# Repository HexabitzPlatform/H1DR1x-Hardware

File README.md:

# H1DR1x-Hardware
Hexabitz RS485 Serial Transceiver Module Hardware Design

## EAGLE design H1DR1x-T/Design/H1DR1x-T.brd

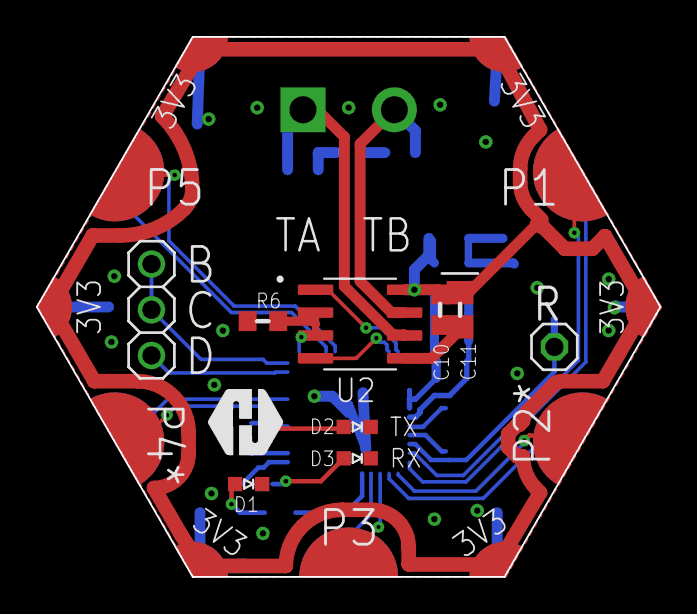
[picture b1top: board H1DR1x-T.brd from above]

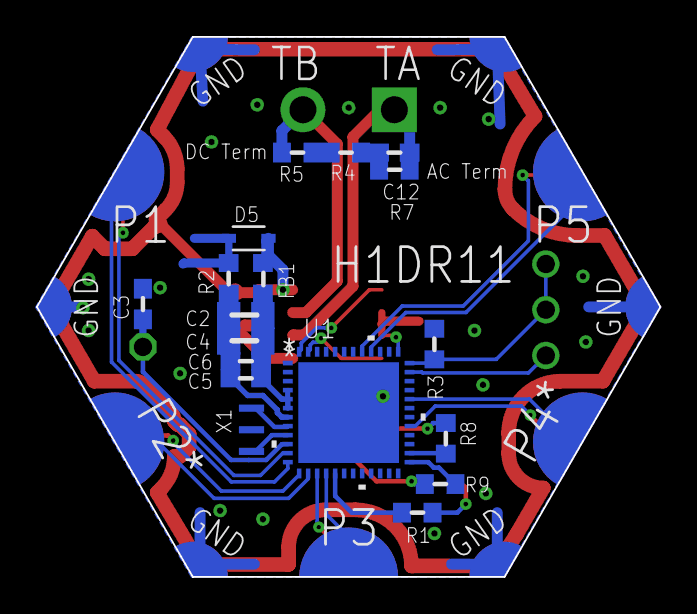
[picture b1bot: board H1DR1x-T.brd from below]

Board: 2 copper layers, 34.6 x 30.0 mm, 30 parts (18 on the bottom side), 32 nets.

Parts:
C2: 1uF; C-0805
C3, C5, C6, C10, C12: 100nF; C-0603
C4: 4.7uF; C-0805
C11: 4.7uF; C-0805-POL
D1: RED; VLMS1300-GS08
D2: YELLOW; VLMS1300-GS08
D3: ORANGE; VLMS1300-GS08
D5: BOURNS_CDSOD323-T03SCBOURNS_CDSOD323-T03SC_0_0; BOURNS_CDSOD323-T03SC_0
FB1: FB-TDK_MMZ1608Y300B; FB-0603
P1: HEXABIT_17.32_NO_P6
P2: RS-485; 1546111-2
R: R; 1X01
R1, R8, R9: 270R; R-0603
R2, R4, R7: 0.0R; R-0603
R3: 10K; R-0603
R5: 120R; R-0603
R6: 10k; R-0603
SWD: 1X03
TRIMBLE-LOGO1: HEXA-LOGO
U1: STM32G0B1CEU6QFN_B1CEU6_STM-L; QFN_B1CEU6_STM-L
U2: MAX14840EASA+T; SOIC127P600X175-8N
X1: XTALL_CSTCE8M00G52

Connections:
CLK: R3.2, SWD.1, SWD.2, U1.36
DATA: SWD.3, U1.35
GND: C3.2, C10.2, C11.2, D1.C, D2.C, D3.C, D5.1, P1.PAD_PD7, P1.PAD_PD8, P1.PAD_PD9, P1.PAD_PD10, P1.PAD_PD11, P1.PAD_PD12, R2.1, R3.1, R6.2, U1.49, U2.5, X1.P$2
unnamed: D1.A, R1.2
unnamed: C12.2, R4.2, R7.1
unnamed: R1.1, U1.17
unnamed: C3.1, R.1, U1.10
unnamed: U1.9, X1.P$1
unnamed: U1.8, X1.P$3
unnamed: R4.1, R5.2
unnamed: D3.A, R9.1
unnamed: D2.A, R8.1
RX_LED: R9.2, U1.25
TA: C12.1, P2.1, R7.2, U2.6
TB: P2.2, R5.1, U2.7
TX_LED: R8.2, U1.26
USART1_RX: P1.PAD_PD4, U1.32
USART1_TX: P1.PAD_PU4, U1.29
USART2_RX: P1.PAD_PD2, U1.14
USART2_TX: P1.PAD_PU2, U1.13
USART3_RTS: R6.1, U1.37, U2.2, U2.3
USART3_RX: U1.48, U2.1
USART3_TX: U1.47, U2.4
USART4_RX: P1.PAD_PD1, U1.12
USART4_TX: P1.PAD_PU1, U1.11
USART5_RX: P1.PAD_PD5, U1.40
USART5_TX: P1.PAD_PU5, U1.41
USART6_RX: P1.PAD_PD3, U1.16
USART6_TX: P1.PAD_PU3, U1.15
VDD: C10.1, C11.1, D5.2, FB1.2, P1.PAD_PU7, P1.PAD_PU8, P1.PAD_PU9, P1.PAD_PU10, P1.PAD_PU11, P1.PAD_PU12, U2.8
VDDA: C2.1, C4.1, C5.1, C6.1, FB1.1, U1.4, U1.5, U1.6
VSSA: C2.2, C4.2, C5.2, C6.2, R2.2, U1.7

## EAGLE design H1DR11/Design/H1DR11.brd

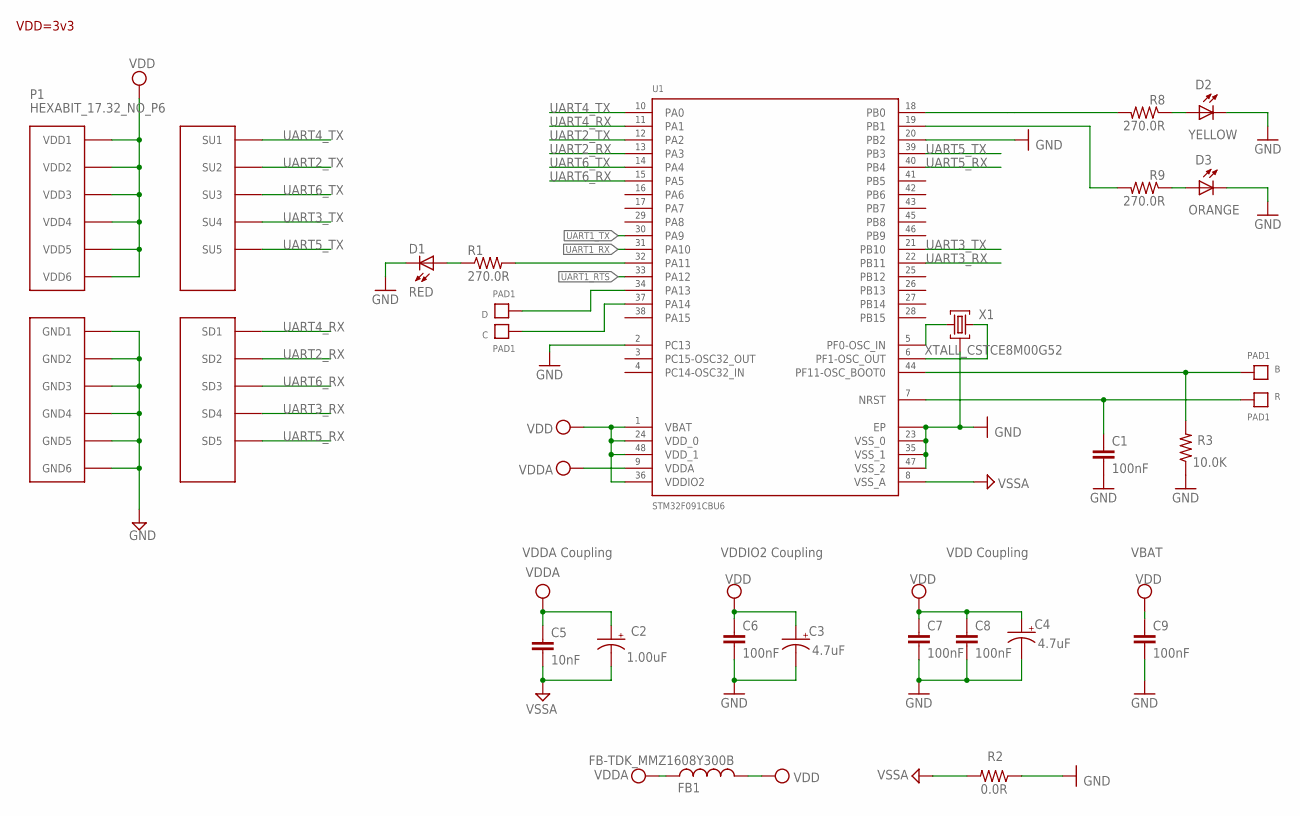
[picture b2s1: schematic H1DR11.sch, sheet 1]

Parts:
B: PAD1
C: PAD1
C1, C6, C8: 100nF; C-0603; TOLERANCE 10%; VOLTAGE_RATING 10V; MPN C0603C104K8RACTU
C2: 1.00uF; C-0805-POL; TOLERANCE 10%; VOLTAGE_RATING 16V; MPN CC0805KKX7R7BB105
C3, C4: 4.7uF; C-0805-POL; TOLERANCE 10%; VOLTAGE_RATING 25V; MPN GRM21BC81E475KA12L
C5: 10nF; C-0603; TOLERANCE 10%; VOLTAGE_RATING 50V; MPN C0603C103K5RACTU
C7: 100nF; C-0603; TOLERANCE 10%; VOLTAGE_RATING 10; MPN C0603C104K8RACTU
C9: 100nF; C-0603; TOLERANCE 10V; VOLTAGE_RATING 10%; MPN C0603C104K8RACTU
D: PAD1
D1: RED; VLMS1300-GS08; MPN VLMS1300-GS08
D2: YELLOW; VLMS1300-GS08; MPN VLMY1300-GS08
D3: ORANGE; VLMS1300-GS08; MPN VLMO1300-GS08
FB1: FB-TDK_MMZ1608Y300B; MPN MMZ1608Y300B
P1: HEXABIT_17.32_NO_P6
R: PAD1
R1, R8, R9: 270.0R; R-0603; TOLERANCE 1%; MPN RC0603FR-07270RL
R2: 0.0R; R-0603; MPN RC0603JR-070RL
R3: 10.0K; R-0603; TOLERANCE 5%; MPN RC0603JR-0710KL
U1: STM32F091CBU6
X1: XTALL_CSTCE8M00G52

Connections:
B1: B.P$1, B.P$2, R3.2, U1.P$44 (PF11-OSC_BOOT0)
GND: C1.2, C3.2 (-), C4.2 (-), C6.2, C7.2, C8.2, C9.2, D1.C, D2.C, D3.C, P1.PAD_PD7 (GND1), P1.PAD_PD8 (GND2), P1.PAD_PD9 (GND3), P1.PAD_PD10 (GND4), P1.PAD_PD11 (GND5), P1.PAD_PD12 (GND6), R2.1, R3.1, U1.EP, U1.P$2 (PC13), U1.P$20 (PB2), U1.P$23 (VSS_0), U1.P$35 (VSS_1), U1.P$47 (VSS_2), X1.P$2 (2); also elsewhere on the board
unnamed: D.P$1, D.P$2, U1.P$34 (PA13)
unnamed: R1.2, U1.P$32 (PA11)
unnamed: D1.A, R1.1
unnamed: U1.P$5 (PF0-OSC_IN), X1.P$1 (1)
unnamed: U1.P$6 (PF1-OSC_OUT), X1.P$3 (3)
unnamed: C.P$1, C.P$2, U1.P$37 (PA14)
unnamed: R8.2, U1.P$18 (PB0)
unnamed: D2.A, R8.1
unnamed: R9.2, U1.P$19 (PB1)
unnamed: D3.A, R9.1
R1: C1.1, R.P$1, R.P$2, U1.P$7 (NRST)
UART1_RTS: U1.P$33 (PA12); also elsewhere on the board
UART1_RX: U1.P$31 (PA10); also elsewhere on the board
UART1_TX: U1.P$30 (PA9); also elsewhere on the board
UART2_RX: P1.PAD_PD2 (SD2), U1.P$13 (PA3)
UART2_TX: P1.PAD_PU2 (SU2), U1.P$12 (PA2)
UART3_RX: P1.PAD_PD4 (SD4), U1.P$22 (PB11)
UART3_TX: P1.PAD_PU4 (SU4), U1.P$21 (PB10)
UART4_RX: P1.PAD_PD1 (SD1), U1.P$11 (PA1)
UART4_TX: P1.PAD_PU1 (SU1), U1.P$10 (PA0)
UART5_RX: P1.PAD_PD5 (SD5), U1.P$40 (PB4)
UART5_TX: P1.PAD_PU5 (SU5), U1.P$39 (PB3)
UART6_RX: P1.PAD_PD3 (SD3), U1.P$15 (PA5)
UART6_TX: P1.PAD_PU3 (SU3), U1.P$14 (PA4)
VDD: C3.1 (+), C4.1 (+), C6.1, C7.1, C8.1, C9.1, FB1.2, P1.PAD_PU7 (VDD1), P1.PAD_PU8 (VDD2), P1.PAD_PU9 (VDD3), P1.PAD_PU10 (VDD4), P1.PAD_PU11 (VDD5), P1.PAD_PU12 (VDD6), U1.P$1 (VBAT), U1.P$24 (VDD_0), U1.P$36 (VDDIO2), U1.P$48 (VDD_1); also elsewhere on the board
VDDA: C2.1 (+), C5.1, FB1.1, U1.P$9 (VDDA)
VSSA: C2.2 (-), C5.2, R2.2, U1.P$8 (VSS_A)

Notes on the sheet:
VDDA Coupling
VDDIO2 Coupling
VDD Coupling
VBAT
VDD=3v3

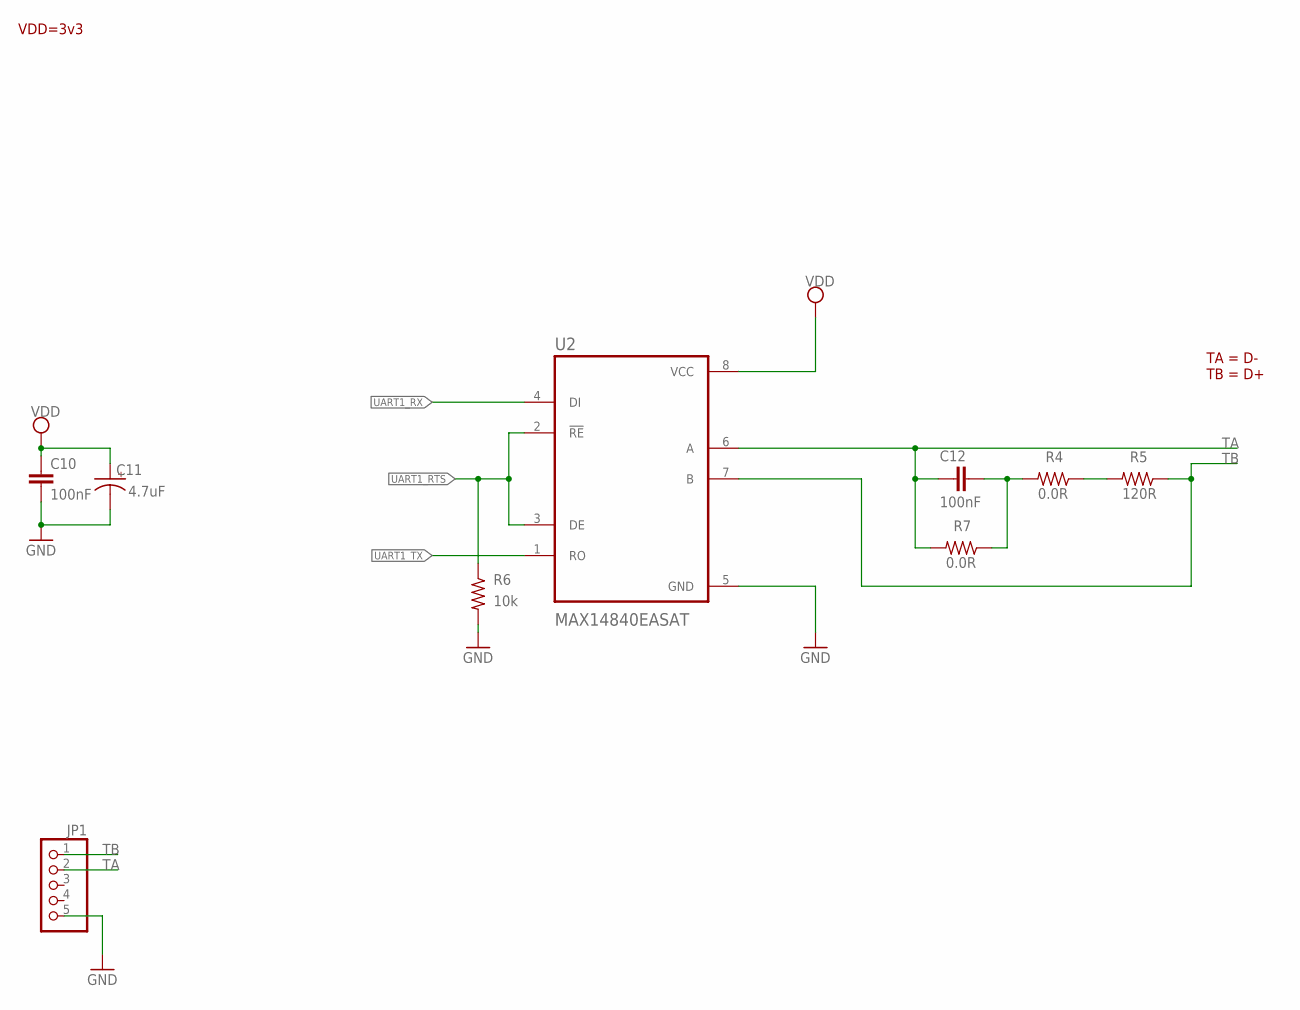
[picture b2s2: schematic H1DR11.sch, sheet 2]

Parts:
C10: 100nF; C-0603; TOLERANCE 10%; VOLTAGE_RATING 10V; MPN C0603C104K8RACTU
C11: 4.7uF; C-0805-POL; TOLERANCE 10%; VOLTAGE_RATING 25V; MPN GRM21BC81E475KA12L
C12: 100nF; C-0603; TOLERANCE 10%; VOLTAGE_RATING 16V; MPN 0603YC104K4T2A
JP1: PINHD-1X5/90; 1X05/90; MPN PEC05SBAN
R4: 0.0R; R-0603; MPN DNP
R5: 120R; R-0805; TOLERANCE 1%; MPN ERJP6WF1200V
R6: 10k; R-0603; TOLERANCE 5%; MPN CRCW060310K0JNEB
R7: 0.0R; R-0603; MPN CRCW06030000Z0EA
U2: MAX14840EASAT; SOIC127P600X175-8N

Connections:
GND: C10.2, C11.2 (-), JP1.5, R6.2, U2.5 (GND); also elsewhere on the board
unnamed: C12.2, R4.2, R7.1
unnamed: R4.1, R5.2
TA: C12.1, JP1.2, R7.2, U2.6 (A)
TB: JP1.1, R5.1, U2.7 (B)
UART1_RTS: R6.1, U2.2 (!RE), U2.3 (DE); also elsewhere on the board
UART1_RX: U2.4 (DI); also elsewhere on the board
UART1_TX: U2.1 (RO); also elsewhere on the board
VDD: C10.1, C11.1 (+), U2.8 (VCC); also elsewhere on the board

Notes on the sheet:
VDD=3v3
TA = D- TB = D+

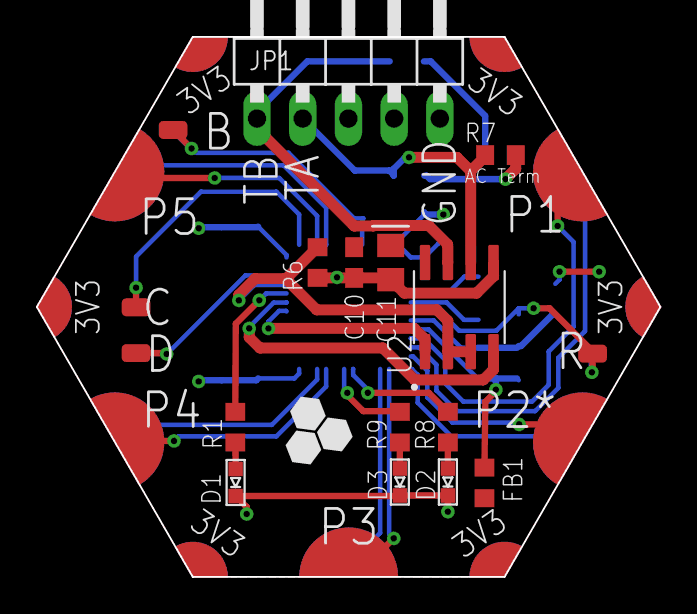
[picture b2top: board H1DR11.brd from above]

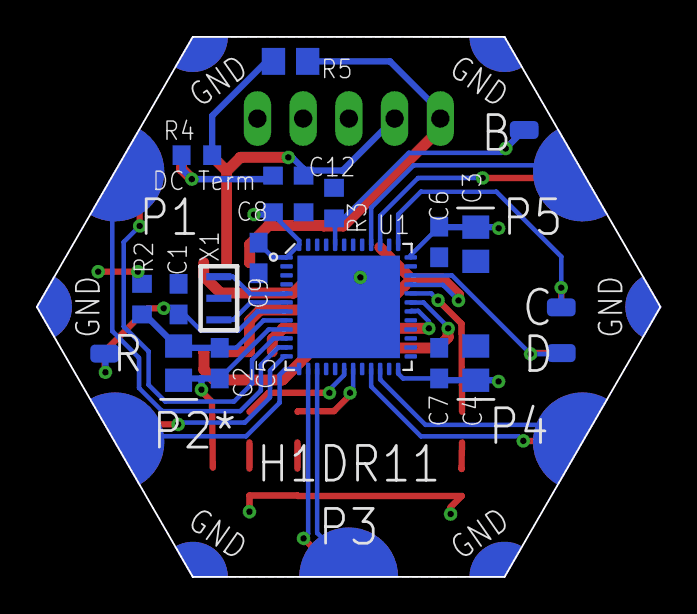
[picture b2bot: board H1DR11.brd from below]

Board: 2 copper layers, 34.6 x 30.0 mm, 34 parts (16 on the bottom side), 33 nets.

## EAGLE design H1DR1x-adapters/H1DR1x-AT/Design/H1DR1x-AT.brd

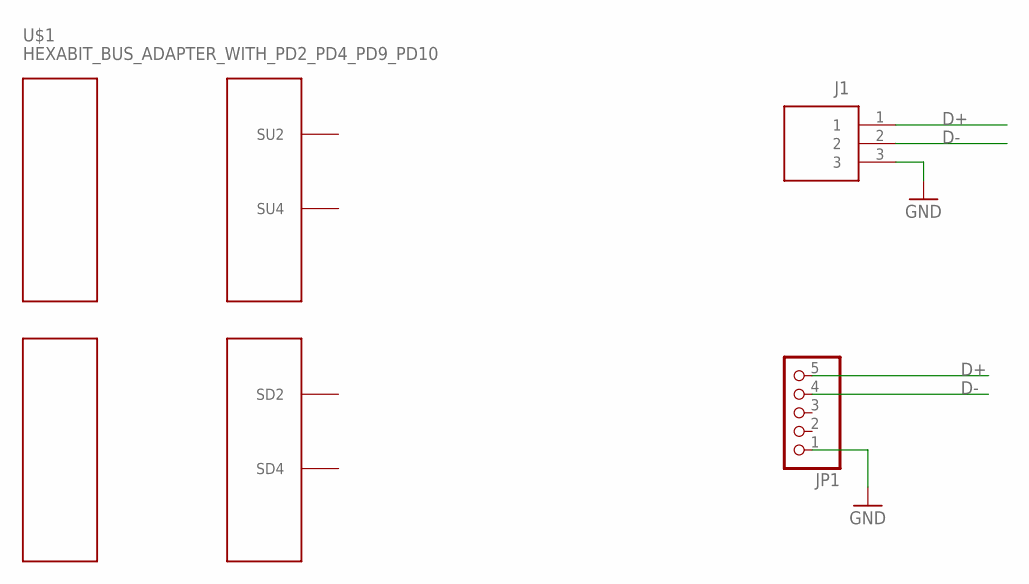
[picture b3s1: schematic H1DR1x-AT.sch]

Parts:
J1: CON-PHOENIX-350_1755749; SHDR3W100P0X508_1X3_1724X860X1; MPN 1755749
JP1: PINHD-1X5; F_1X05; MPN PPTC051LGBN-RC
U$1: HEXABIT_BUS_ADAPTER_WITH_PD2_PD4_PD9_PD10; HEXABIT_BUS_ADAPTER_WITH_P2_P4

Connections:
D+: J1.1, JP1.5
D-: J1.2, JP1.4
GND: J1.3, JP1.1

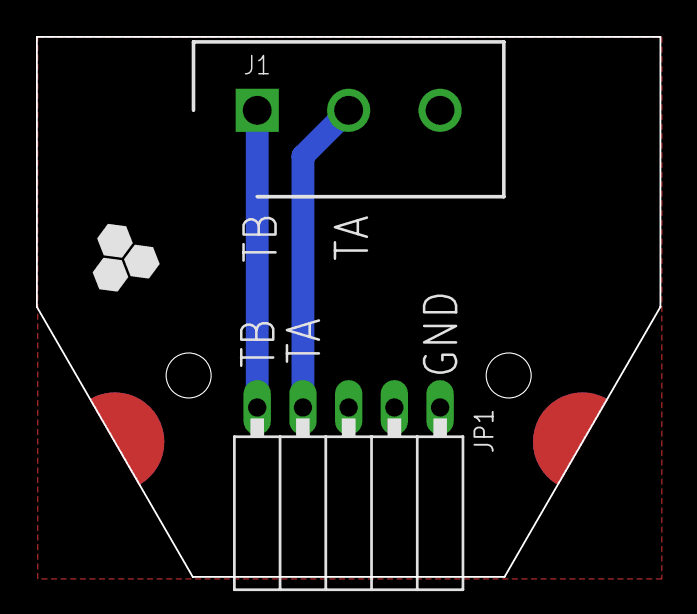
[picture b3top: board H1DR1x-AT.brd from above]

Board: 2 copper layers, 34.6 x 30.0 mm, 3 parts (0 on the bottom side), 3 nets.

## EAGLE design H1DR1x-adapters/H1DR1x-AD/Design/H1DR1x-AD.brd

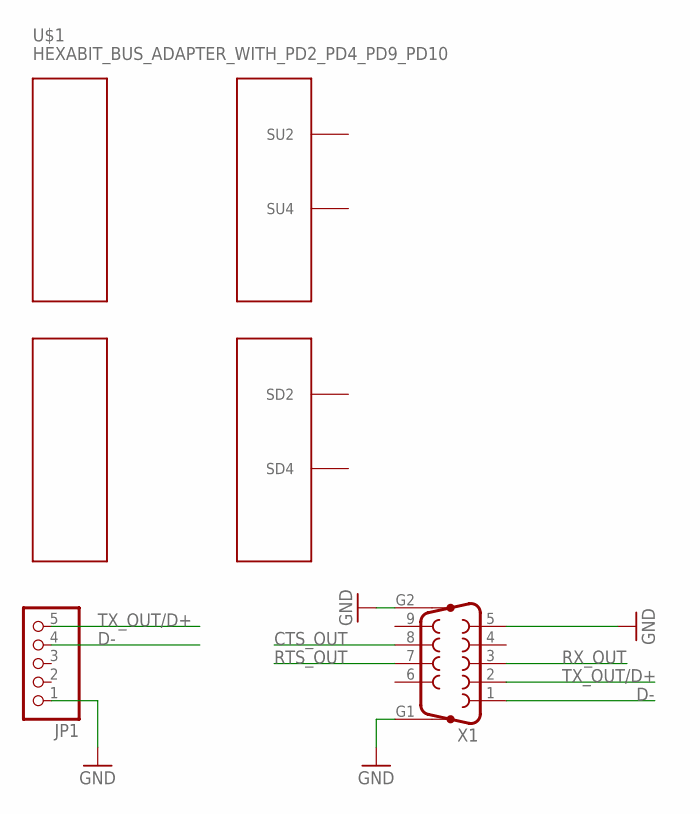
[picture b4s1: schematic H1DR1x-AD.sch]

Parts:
JP1: PINHD-1X5; F_1X05
U$1: HEXABIT_BUS_ADAPTER_WITH_PD2_PD4_PD9_PD10; HEXABIT_BUS_ADAPTER_WITH_P2_P4
X1: F09HP

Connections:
CTS_OUT: X1.8
D-: JP1.4, X1.1
GND: JP1.1, X1.5, X1.G1, X1.G2
RTS_OUT: X1.7
RX_OUT: X1.3
TX_OUT/D+: JP1.5, X1.2

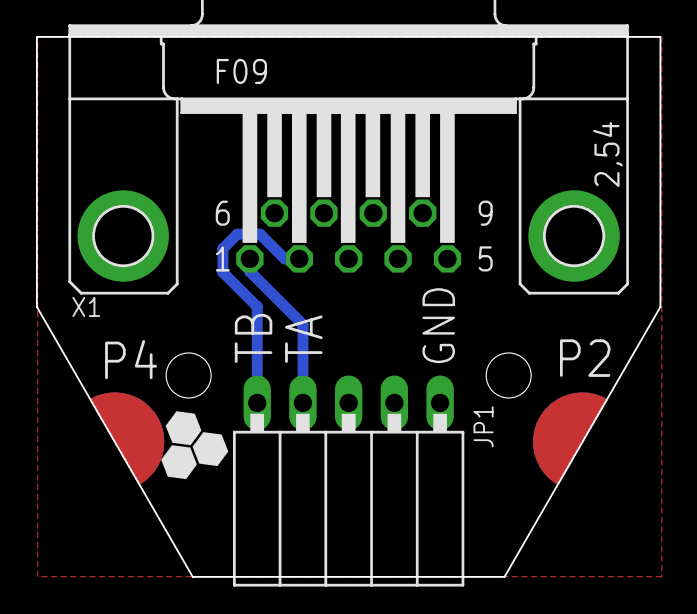
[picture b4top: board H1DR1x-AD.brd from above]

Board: 2 copper layers, 34.6 x 30.0 mm, 3 parts (0 on the bottom side), 3 nets.

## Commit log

2020-03-15 Adding template files
2020-03-24 full unchecked
2020-03-24 Remove temp files
2020-03-26 adding two leds , change the revigion , DRC & ERC checked
2020-04-19 chnage connecter to pinheader
2020-04-20 fix connector problems
2020-04-22 labeling bugs fixed
2020-04-26 mirror pin header
2020-04-27 DB9 adapter was ADDED
2020-04-27 3way terminal block was added
2020-05-28 output CAM files generated
2020-06-12 no message
2020-06-14 Adding schematics PDF Rev 1 module Rev 0 adapters Tagging as rev 1
2024-10-01 - New F0 version for the module RS458 with a terminal block connector. Pin headers for the program have been added for the counter project.
2024-10-02 - Renamed files to H1DR1x-T. - Deleted Gerber and Drill files.
2024-10-02 - Created new decumentation. - Changed to G0 MCU in schematic.
2024-10-02 - Created Documentation folder and put in it the pdf file.
2024-10-02 - Few fixes in schematics. - Regenerated documentation file.
2024-10-02 - Fixed schematics. - Regenerated documentation.
2024-10-03 - Drew PCB.
2024-10-03 - Created output files. - Gerber, Drills and pick and place files are ready.
2024-10-03 - Regenerated Documentation. - BOM is ready. - Regenerated output files.
2024-10-27 - Fixed some mistakes in BOM.
2024-10-27 - Fixed few issues in Schematic. - Regenerated documentation. - Redrew PCB.
2024-10-30 - Fixed BOM issues.
2024-10-30 - Fixed issues in PCB. - Regenerated output files.
2024-11-24 Everything is finished. I fixed some issues and reviewed everything.
2024-12-12 - Fixed description in BOM - Deleted unnecessary file
2025-01-15 Restore Original files

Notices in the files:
parts and their libraries:
COPYRIGHT: Copyright (C) 2021 Ultra Librarian. All rights reserved.
